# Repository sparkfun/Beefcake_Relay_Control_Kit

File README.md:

Beefcake Relay Control Kit
==========================

[  
*Beefcake Relay Control Kit (KIT-13815)*](https://www.sparkfun.com/products/13815)

The Beefcake Relay Control Kit contains all the parts you need to get your high-power load under control.

Repository Contents
-------------------

* **/Hardware** - Eagle design files (Schematic and Board)

Documentation
--------------
* **[Hookup Guide](https://learn.sparkfun.com/tutorials/beefcake-relay-control-hookup-guide)** - Basic hookup guide for the Beefcake Relay Control Kit.
* **[SparkFun Fritzing repo](https://github.com/sparkfun/Fritzing_Parts)** - Fritzing diagrams for SparkFun products.

Product Versions
----------------
* [KIT-13815](https://www.sparkfun.com/products/13815) - Beefcake Relay Control Kit

Version History
---------------
* [v1.6](https://github.com/sparkfun/Beefcake_Relay_Control_Kit/tree/v1.6) - SPST version
* [v2.0](https://github.com/sparkfun/Beefcake_Relay_Control_Kit/tree/v2.0) - SPDT version

License Information
-------------------

This product is _**open source**_! 

Please review the LICENSE.md file for license information. 

If you have any questions or concerns on licensing, please contact techsupport@sparkfun.com.

Distributed as-is; no warranty is given.

- Your friends at SparkFun.

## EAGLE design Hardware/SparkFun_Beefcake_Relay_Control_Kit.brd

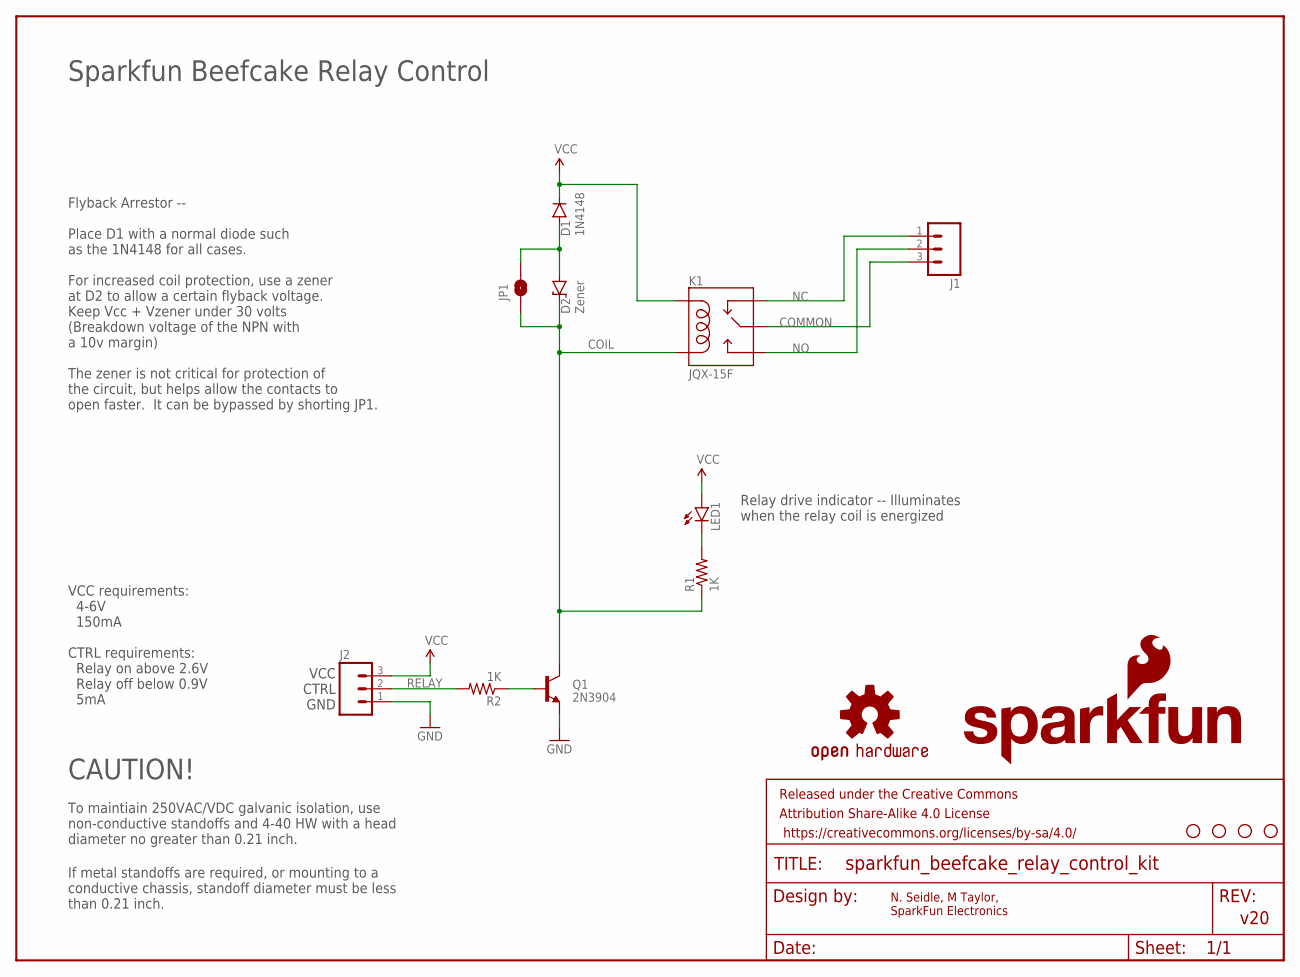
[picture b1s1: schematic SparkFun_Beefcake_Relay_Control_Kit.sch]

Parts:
D1: 1N4148; DIODE-1N4148-KIT
D2: Zener; DIODE-1N4148-KIT
FRAME2: FRAME-LETTER; CREATIVE_COMMONS
J1: M03-SCREW-5MM; SCREWTERMINAL-5MM-3
J2: M03SCREW; SCREWTERMINAL-3.5MM-3
JP1: JUMPER-PAD-2-NOYES_SILK; PAD-JUMPER-2-NO_YES_SILK
K1: JQX-15F; RELAY-T90
LED1: LED5MM-KIT
LOGO1: SFE_LOGO_NAME_FLAME.1_INCH; SFE_LOGO_NAME_FLAME_.1
Q1: 2N3904; TO-92-EZ
R1, R2: 1K; AXIAL-0.3EZ
U$3, U$4, U$5, U$7: STAND-OFF
U$12: OSHW-LOGOS; OSHW-LOGO-S

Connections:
COIL: D2.C, JP1.1, K1.COIL2, Q1.3 (C), R1.P$1 (1)
COMMON: J1.3, K1.MAIN
DIODENODE: D1.A, D2.A, JP1.2
GND: J2.1, Q1.1 (E)
unnamed: Q1.2 (B), R2.P$1 (1)
unnamed: LED1.K (C), R1.P$2 (2)
NC: J1.1, K1.NC
NO: J1.2, K1.NO
RELAY: J2.2, R2.P$2 (2)
VCC: D1.C, J2.3, K1.COIL1, LED1.A

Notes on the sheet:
N. Seidle, M Taylor, SparkFun Electronics
v20
Relay drive indicator -- Illuminates when the relay coil is energized
Flyback Arrestor -- Place D1 with a normal diode such as the 1N4148 for all cases. For increased coil protection, use a zener at D2 to allow a certain flyback voltage. Keep Vcc + Vzener under 30 volts (Breakdown voltage of the NPN with a 10v margin) The zener is not critical for protection of the c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
To maintiain 250VAC/VDC galvanic isolation, use non-conductive standoffs and 4-40 HW with a head diameter no greater than 0.21 inch.
CAUTION!
If metal standoffs are required, or mounting to a conductive chassis, standoff diameter must be less than 0.21 inch.
VCC requirements: 4-6V 150mA CTRL requirements: Relay on above 2.6V Relay off below 0.9V 5mA
VCC CTRL GND
Sparkfun Beefcake Relay Control

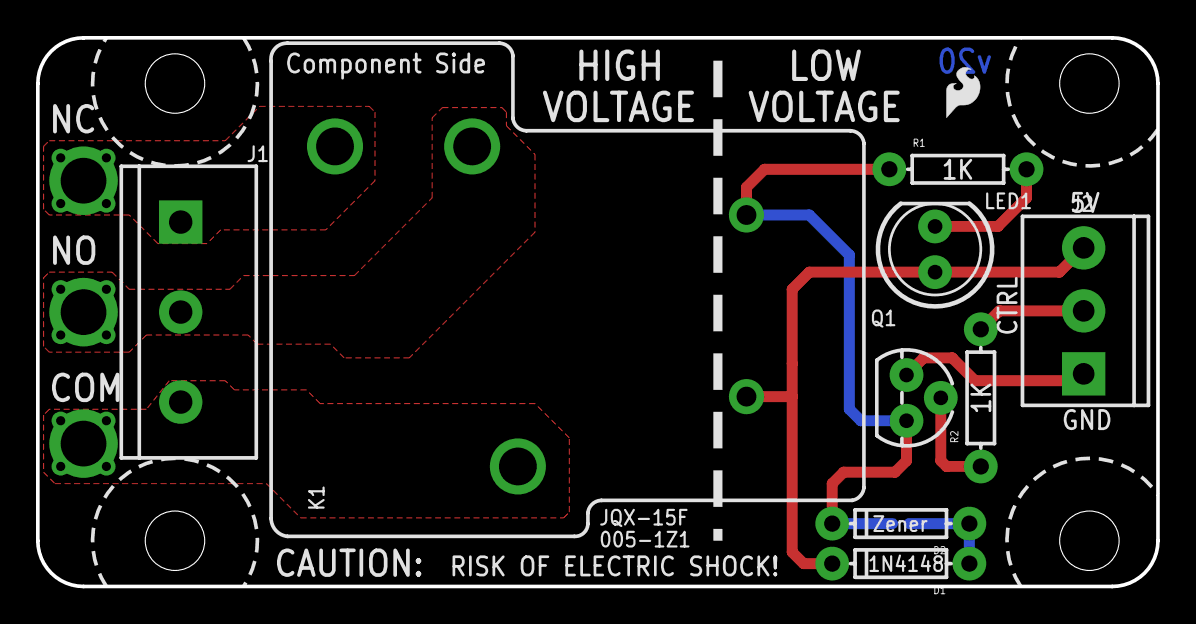
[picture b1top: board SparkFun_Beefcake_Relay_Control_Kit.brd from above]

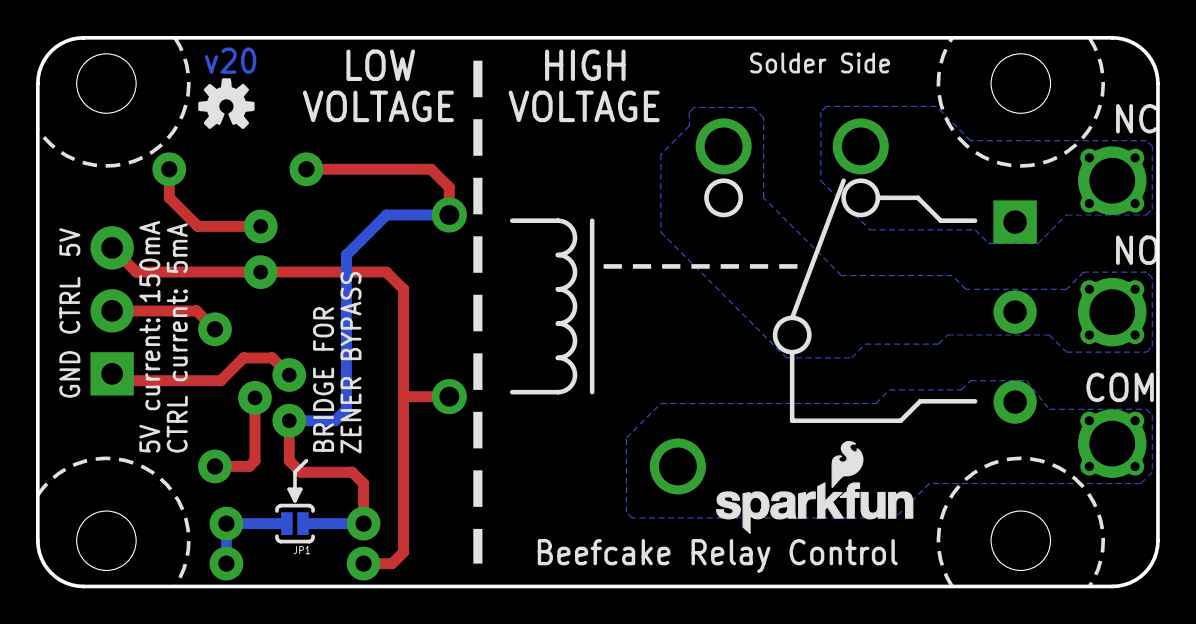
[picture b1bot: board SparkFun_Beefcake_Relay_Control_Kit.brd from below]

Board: 2 copper layers, 62.2 x 30.5 mm, 18 parts (3 on the bottom side), 10 nets.

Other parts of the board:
U$11: SFE-LOGO-FLAME

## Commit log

2014-01-31 initial v17 eagle files
    -gitignore and readme update.
    -updated frame
    -added version to bottom copper
2015-01-19 Updating file names
2015-01-19 Update to current board files
2016-01-29 Design ready for proto 1 review
2016-02-01 Running through review changes
2016-02-01 Ready for QC's review
2016-02-03 updated bom
2016-04-04 updated silk for redboard review
2016-04-05 Finished for reds review, implemented changes
2016-04-05 prepping for QC action
2016-04-07 Resolved github issues
2016-04-07 updated designators
2016-06-02 Pointed pictures and links to new product listing, preparing for merge, fixed typo in schematic text
2016-06-02 Updated readme to template standard
2016-06-02 Added documentation links in readme

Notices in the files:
parts and their libraries:
SparkFun-Aesthetics: Licensing: CC v3.0 Share-Alike You are welcome to use this library for commercial purposes.
SparkFun-Aesthetics: Released under the Creative Commons Attribution Share-Alike 4.0 License
SparkFun-Aesthetics: https://creativecommons.org/licenses/by-sa/4.0
